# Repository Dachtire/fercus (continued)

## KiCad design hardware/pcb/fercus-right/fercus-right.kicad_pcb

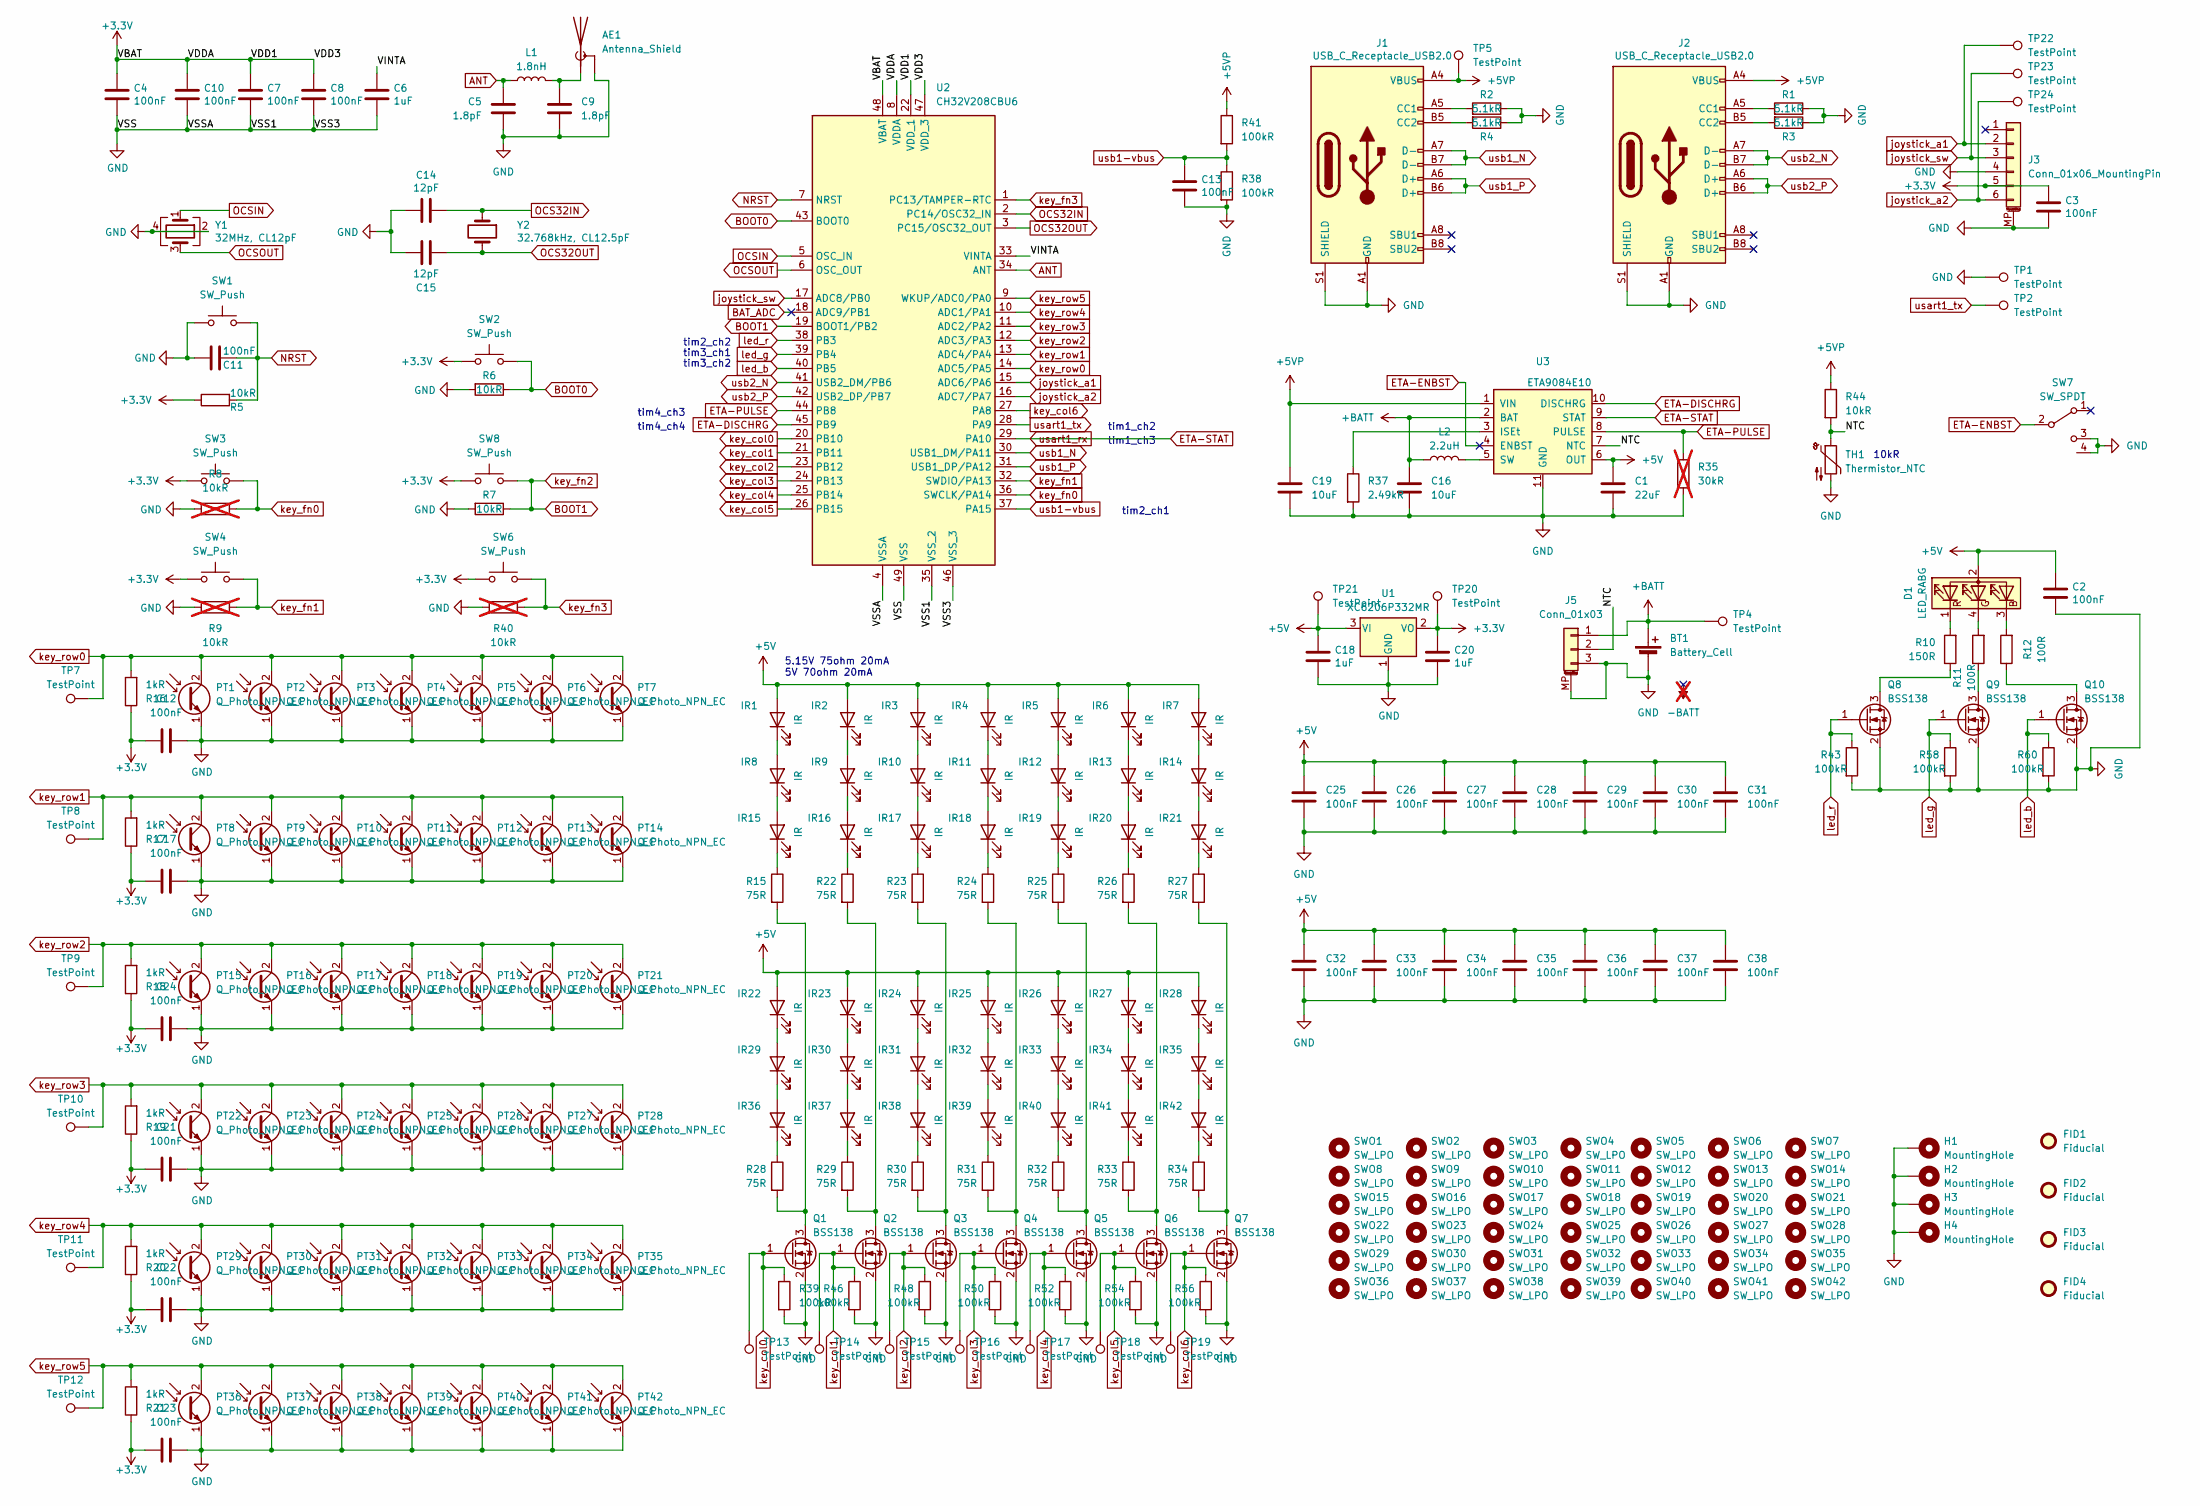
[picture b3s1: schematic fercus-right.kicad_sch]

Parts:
AE1: Antenna_Shield; ANT-F-1-2.4G-1.2MM-FR4-WCH_Right_NoMask
BT1: Battery_Cell
C1: 22uF; C_0603_1608Metric
C2, C3, C12, C13, C17, C21, C22, C23, C24, C25, C26, C27, C28, C29, C30, C31, C32, C33, C34, C35, C36, C37, C38: 100nF; C_0603_1608Metric
C4, C7, C8, C10, C11: 100nF; C_0402_1005Metric
C5, C9: 1.8pF; C_0402_1005Metric
C6: 1uF; C_0402_1005Metric
C14, C15: 12pF; C_0402_1005Metric
C16: 10uF; C_0603_1608Metric
C18, C20: 1uF; C_0603_1608Metric
C19: 10uF; C_0805_2012Metric
D1: LED_RABG; Everlight_LED_RGB_PLCC-4
FID1, FID2, FID3, FID4: Fiducial; Fiducial_1mm_Mask3mm
H1, H2, H3, H4: MountingHole; MountingHole_2.2mm_M2_ISO14580_Pad
IR1, IR2, IR3, IR4, IR5, IR6, IR7, IR8, IR9, IR10, IR11, IR12, IR13, IR14, IR15, IR16, IR17, IR18, IR19, IR20, IR21, IR22, IR23, IR24, IR25, IR26, IR27, IR28, IR29, IR30, IR31, IR32, IR33, IR34, IR35, IR36, IR37, IR38, IR39, IR40, IR41, IR42: IR; KTR-0602IRC
J1, J2: USB_C_Receptacle_USB2.0; USB_C_Receptacle_HRO_TYPE-C-31-M-12
J3: Conn_01x06_MountingPin; Jushuo_AFC42-S06FMA-1H_1x6-1MP_P0.50_Horizontal
J5: Conn_01x03; Molex_PicoBlade_53261-0371_1x03-1MP_P1.25mm_Horizontal
L1: 1.8nH; L_0402_1005Metric
L2: 2.2uH; L_Sunlord_MWSA0402S
PT1, PT2, PT3, PT4, PT5, PT6, PT7, PT8, PT9, PT10, PT11, PT12, PT13, PT14, PT15, PT16, PT17, PT18, PT19, PT20, PT21, PT22, PT23, PT24, PT25, PT26, PT27, PT28, PT29, PT30, PT31, PT32, PT33, PT34, PT35, PT36, PT37, PT38, PT39, PT40, PT41, PT42: Q_Photo_NPN_EC; KTR-0602PTD
Q1, Q2, Q3, Q4, Q5, Q6, Q7, Q8, Q9, Q10: BSS138; SOT-23
R1, R2, R3, R4: 5.1kR; R_0603_1608Metric
R5, R6, R7, R44: 10kR; R_0603_1608Metric
R8, R9, R40: 10kR; R_0603_1608Metric; not fitted
R10: 150R; R_0603_1608Metric
R11, R12: 100R; R_0603_1608Metric
R15, R22, R23, R24, R25, R26, R27, R28, R29, R30, R31, R32, R33, R34: 75R; R_0603_1608Metric
R16, R17, R18, R19, R20, R21: 1kR; R_0603_1608Metric
R35: 30kR; R_0603_1608Metric; not fitted
R37: 2.49kR; R_0603_1608Metric
R38, R39, R41, R43, R46, R48, R50, R52, R54, R56, R58, R60: 100kR; R_0603_1608Metric
SW1, SW2, SW3, SW4, SW6, SW8: SW_Push; SW_SPST_TL3342
SW7: SW_SPDT; SW_SPDT_PCM12
SWO1, SWO2, SWO3, SWO4, SWO5, SWO6, SWO7, SWO8, SWO9, SWO10, SWO11, SWO12, SWO13, SWO14, SWO15, SWO16, SWO17, SWO18, SWO19, SWO20, SWO21, SWO22, SWO23, SWO24, SWO25, SWO26, SWO27, SWO28, SWO29, SWO30, SWO31, SWO32, SWO33, SWO34, SWO35, SWO36, SWO37, SWO38, SWO39, SWO40, SWO41, SWO42: SW_LPO; SW_RAESHA_Low_Profile_Optical
TH1: Thermistor_NTC; R_0603_1608Metric
TP1, TP2, TP4, TP5, TP7, TP8, TP9, TP10, TP11, TP12, TP13, TP14, TP15, TP16, TP17, TP18, TP19, TP20, TP21, TP22, TP23, TP24: TestPoint; TestPoint_Pad_D1.0mm
U1: XC6206P332MR; SOT-23-3
U2: CH32V208CBU6; QFN-48-1EP_5x5mm_P0.35mm_EP3.7x3.7mm_ThermalVias_Drill0.3mm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
U3: ETA9084E10; SSOP-10-1EP_3.9x4.9mm_P1.00mm_EP2.4x2.8mm_ThermalVias_Drill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
Y1: 32MHz, CL12pF; Crystal_SMD_2016-4Pin_2.0x1.6mm
Y2: 32.768kHz, CL12.5pF; Crystal_SMD_2012-2Pin_2.0x1.2mm

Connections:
+3.3V: C3.1, C4.1, C7.1, C8.1, C10.1, C12.1, C17.1, C20.1, C21.1, C22.1, C23.1, C24.1, J3.5, R5.1, R16.1, R17.1, R18.1, R19.1, R20.1, R21.1, SW2.1, SW3.1, SW4.1, SW6.1, SW8.1, TP20.1, U1.2 (VO), U2.8 (VDDA), U2.22 (VDD_1), U2.47 (VDD_3), U2.48 (VBAT)
+5V: C1.1, C2.1, C18.1, C25.2, C26.2, C27.2, C28.2, C29.2, C30.2, C31.2, C32.2, C33.2, C34.2, C35.2, C36.2, C37.2, C38.2, D1.2 (A), IR1.2 (A), IR2.2 (A), IR3.2 (A), IR4.2 (A), IR5.2 (A), IR6.2 (A), IR7.2 (A), IR22.2 (A), IR23.2 (A), IR24.2 (A), IR25.2 (A), IR26.2 (A), IR27.2 (A), IR28.2 (A), TP21.1, U1.3 (VI), U3.6 (OUT)
+5VP: C19.1, J1.A4 (VBUS), J1.A9 (VBUS), J1.B4 (VBUS), J1.B9 (VBUS), J2.A4 (VBUS), J2.A9 (VBUS), J2.B4 (VBUS), J2.B9 (VBUS), R41.1, R44.1, TP5.1, U3.1 (VIN)
+BATT: BT1.1 (+), C16.1, J5.1, L2.1, TP4.1, U3.2 (BAT)
/NTC: J5.2, R44.2, TH1.1, U3.7 (NTC)
/VINTA: C6.1, U2.33 (VINTA)
ANT: C5.1, L1.1, U2.34 (ANT)
BAT_ADC: U2.18 (ADC9/PB1)
BOOT0: R6.1, SW2.2, U2.43 (BOOT0)
BOOT1: R7.1, SW8.2, U2.19 (BOOT1/PB2)
ETA-DISCHRG: U2.45 (PB9), U3.10 (DISCHRG)
ETA-ENBST: SW7.2 (B), U3.4 (ENBST)
ETA-PULSE: R35.1, U2.44 (PB8), U3.8 (PULSE)
ETA-STAT: U2.29 (PA10), U3.9 (STAT)
GND: AE1.2 (Shield), BT1.2 (-), C1.2, C2.2, C3.2, C4.2, C5.2, C6.2, C7.2, C8.2, C9.2, C10.2, C11.2, C12.2, C13.2, C14.2, C15.2, C16.2, C17.2, C18.2, C19.2, C20.2, C21.2, C22.2, C23.2, C24.2, C25.1, C26.1, C27.1, C28.1, C29.1, C30.1, C31.1, C32.1, C33.1, C34.1, C35.1, C36.1, C37.1, C38.1, H1.1, H2.1, H3.1, H4.1, J1.A1 (GND), J1.A12 (GND), J1.B1 (GND), J1.B12 (GND), J1.S1 (SHIELD), J2.A1 (GND), J2.A12 (GND), J2.B1 (GND), J2.B12 (GND), J2.S1 (SHIELD), J3.4, J3.MP (MountPin), J5.3, J5.MP (MountPin), PT1.1 (E), PT2.1 (E), PT3.1 (E), PT4.1 (E), PT5.1 (E), PT6.1 (E), PT7.1 (E), PT8.1 (E), PT9.1 (E), PT10.1 (E), PT11.1 (E), PT12.1 (E), PT13.1 (E), PT14.1 (E), PT15.1 (E), PT16.1 (E), PT17.1 (E), PT18.1 (E), PT19.1 (E), PT20.1 (E), PT21.1 (E), PT22.1 (E), PT23.1 (E), PT24.1 (E), PT25.1 (E), PT26.1 (E), PT27.1 (E), PT28.1 (E), PT29.1 (E), PT30.1 (E), PT31.1 (E), PT32.1 (E), PT33.1 (E), PT34.1 (E), PT35.1 (E), PT36.1 (E), PT37.1 (E), PT38.1 (E), PT39.1 (E), PT40.1 (E), PT41.1 (E), PT42.1 (E), Q1.2 (S), Q2.2 (S), Q3.2 (S), Q4.2 (S), Q5.2 (S), Q6.2 (S), Q7.2 (S), Q8.2 (S), Q9.2 (S), Q10.2 (S), R1.1, R2.1, R3.1, R4.1, R6.2, R7.2, R8.2, R9.2, R35.2, R37.2, R38.2, R39.2, R40.2, R43.2, R46.2, R48.2, R50.2, R52.2, R54.2, R56.2, R58.2, R60.2, SW1.1, SW7.3 (C), SW7.4, TH1.2, TP1.1, U1.1 (GND), U2.4 (VSSA), U2.35 (VSS_2), U2.46 (VSS_3), U2.49 (VSS), U3.11 (GND), Y1.2, Y1.4
NRST: C11.1, R5.2, SW1.2, U2.7 (NRST)
unnamed: AE1.1 (A), C9.1, L1.2
unnamed: D1.3 (BK), R12.2
unnamed: D1.4 (GK), R11.2
unnamed: D1.1 (RK), R10.2
unnamed: IR1.1 (K), IR8.2 (A)
unnamed: IR2.1 (K), IR9.2 (A)
unnamed: IR3.1 (K), IR10.2 (A)
unnamed: IR10.1 (K), IR17.2 (A)
unnamed: IR4.1 (K), IR11.2 (A)
unnamed: IR11.1 (K), IR18.2 (A)
unnamed: IR5.1 (K), IR12.2 (A)
unnamed: IR12.1 (K), IR19.2 (A)
unnamed: IR6.1 (K), IR13.2 (A)
unnamed: IR13.1 (K), IR20.2 (A)
unnamed: IR7.1 (K), IR14.2 (A)
unnamed: IR14.1 (K), IR21.2 (A)
unnamed: IR8.1 (K), IR15.2 (A)
unnamed: IR15.1 (K), R15.1
unnamed: IR9.1 (K), IR16.2 (A)
unnamed: IR16.1 (K), R22.1
unnamed: IR17.1 (K), R23.1
unnamed: IR18.1 (K), R24.1
unnamed: IR19.1 (K), R25.1
unnamed: IR20.1 (K), R26.1
unnamed: IR21.1 (K), R27.1
unnamed: IR22.1 (K), IR29.2 (A)
unnamed: IR23.1 (K), IR30.2 (A)
unnamed: IR24.1 (K), IR31.2 (A)
unnamed: IR25.1 (K), IR32.2 (A)
unnamed: IR26.1 (K), IR33.2 (A)
unnamed: IR27.1 (K), IR34.2 (A)
unnamed: IR28.1 (K), IR35.2 (A)
unnamed: IR29.1 (K), IR36.2 (A)
unnamed: IR30.1 (K), IR37.2 (A)
unnamed: IR31.1 (K), IR38.2 (A)
unnamed: IR32.1 (K), IR39.2 (A)
unnamed: IR33.1 (K), IR40.2 (A)
unnamed: IR34.1 (K), IR41.2 (A)
unnamed: IR35.1 (K), IR42.2 (A)
unnamed: IR36.1 (K), R28.1
unnamed: IR37.1 (K), R29.1
unnamed: IR38.1 (K), R30.1
unnamed: IR39.1 (K), R31.1
unnamed: IR40.1 (K), R32.1
unnamed: IR41.1 (K), R33.1
unnamed: IR42.1 (K), R34.1
unnamed: J1.A5 (CC1), R2.2
unnamed: J1.B5 (CC2), R4.2
unnamed: J2.A5 (CC1), R1.2
unnamed: J2.B5 (CC2), R3.2
unnamed: Q1.3 (D), R15.2, R28.2
unnamed: Q2.3 (D), R22.2, R29.2
unnamed: Q3.3 (D), R23.2, R30.2
unnamed: Q4.3 (D), R24.2, R31.2
unnamed: Q5.3 (D), R25.2, R32.2
unnamed: Q6.3 (D), R26.2, R33.2
unnamed: Q7.3 (D), R27.2, R34.2
unnamed: Q8.3 (D), R10.1
unnamed: Q9.3 (D), R11.1
unnamed: Q10.3 (D), R12.1
unnamed: R37.1, U3.3 (ISEt)
unnamed: L2.2, U3.5 (SW)
OCS32IN: C14.1, U2.2 (PC14/OSC32_IN), Y2.1
OCS32OUT: C15.1, U2.3 (PC15/OSC32_OUT), Y2.2
OCSIN: U2.5 (OSC_IN), Y1.1
OCSOUT: U2.6 (OSC_OUT), Y1.3
joystick_a1: J3.2, TP22.1, U2.15 (ADC6/PA6)
joystick_a2: J3.6, TP24.1, U2.16 (ADC7/PA7)
joystick_sw: J3.3, TP23.1, U2.17 (ADC8/PB0)
key_col0: Q1.1 (G), R39.1, TP13.1, U2.20 (PB10)
key_col1: Q2.1 (G), R46.1, TP14.1, U2.21 (PB11)
key_col2: Q3.1 (G), R48.1, TP15.1, U2.23 (PB12)
key_col3: Q4.1 (G), R50.1, TP16.1, U2.24 (PB13)
key_col4: Q5.1 (G), R52.1, TP17.1, U2.25 (PB14)
key_col5: Q6.1 (G), R54.1, TP18.1, U2.26 (PB15)
key_col6: Q7.1 (G), R56.1, TP19.1, U2.27 (PA8)
key_fn0: R8.1, SW3.2, U2.36 (SWCLK/PA14)
key_fn1: R9.1, SW4.2, U2.32 (SWDIO/PA13)
key_fn3: R40.1, SW6.2, U2.1 (PC13/TAMPER-RTC)
key_row0: PT1.2 (C), PT2.2 (C), PT3.2 (C), PT4.2 (C), PT5.2 (C), PT6.2 (C), PT7.2 (C), R16.2, TP7.1, U2.14 (ADC5/PA5)
key_row1: PT8.2 (C), PT9.2 (C), PT10.2 (C), PT11.2 (C), PT12.2 (C), PT13.2 (C), PT14.2 (C), R17.2, TP8.1, U2.13 (ADC4/PA4)
key_row2: PT15.2 (C), PT16.2 (C), PT17.2 (C), PT18.2 (C), PT19.2 (C), PT20.2 (C), PT21.2 (C), R18.2, TP9.1, U2.12 (ADC3/PA3)
key_row3: PT22.2 (C), PT23.2 (C), PT24.2 (C), PT25.2 (C), PT26.2 (C), PT27.2 (C), PT28.2 (C), R19.2, TP10.1, U2.11 (ADC2/PA2)
key_row4: PT29.2 (C), PT30.2 (C), PT31.2 (C), PT32.2 (C), PT33.2 (C), PT34.2 (C), PT35.2 (C), R20.2, TP11.1, U2.10 (ADC1/PA1)
key_row5: PT36.2 (C), PT37.2 (C), PT38.2 (C), PT39.2 (C), PT40.2 (C), PT41.2 (C), PT42.2 (C), R21.2, TP12.1, U2.9 (WKUP/ADC0/PA0)
led_b: Q10.1 (G), R60.1, U2.40 (PB5)
led_g: Q9.1 (G), R58.1, U2.39 (PB4)
led_r: Q8.1 (G), R43.1, U2.38 (PB3)
usart1_tx: TP2.1, U2.28 (PA9)
usb1-vbus: C13.1, R38.1, R41.2, U2.37 (PA15)
usb1_N: J1.A7 (D-), J1.B7 (D-), U2.30 (USB1_DM/PA11)
usb1_P: J1.A6 (D+), J1.B6 (D+), U2.31 (USB1_DP/PA12)
usb2_N: J2.A7 (D-), J2.B7 (D-), U2.41 (USB2_DM/PB6)
usb2_P: J2.A6 (D+), J2.B6 (D+), U2.42 (USB2_DP/PB7)

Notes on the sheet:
10kR
tim4_ch4
tim1_ch3
tim2_ch2
5.15V 75ohm 20mA 5V 70ohm 20mA
tim2_ch1
tim4_ch3
tim1_ch2
tim3_ch2
tim3_ch1

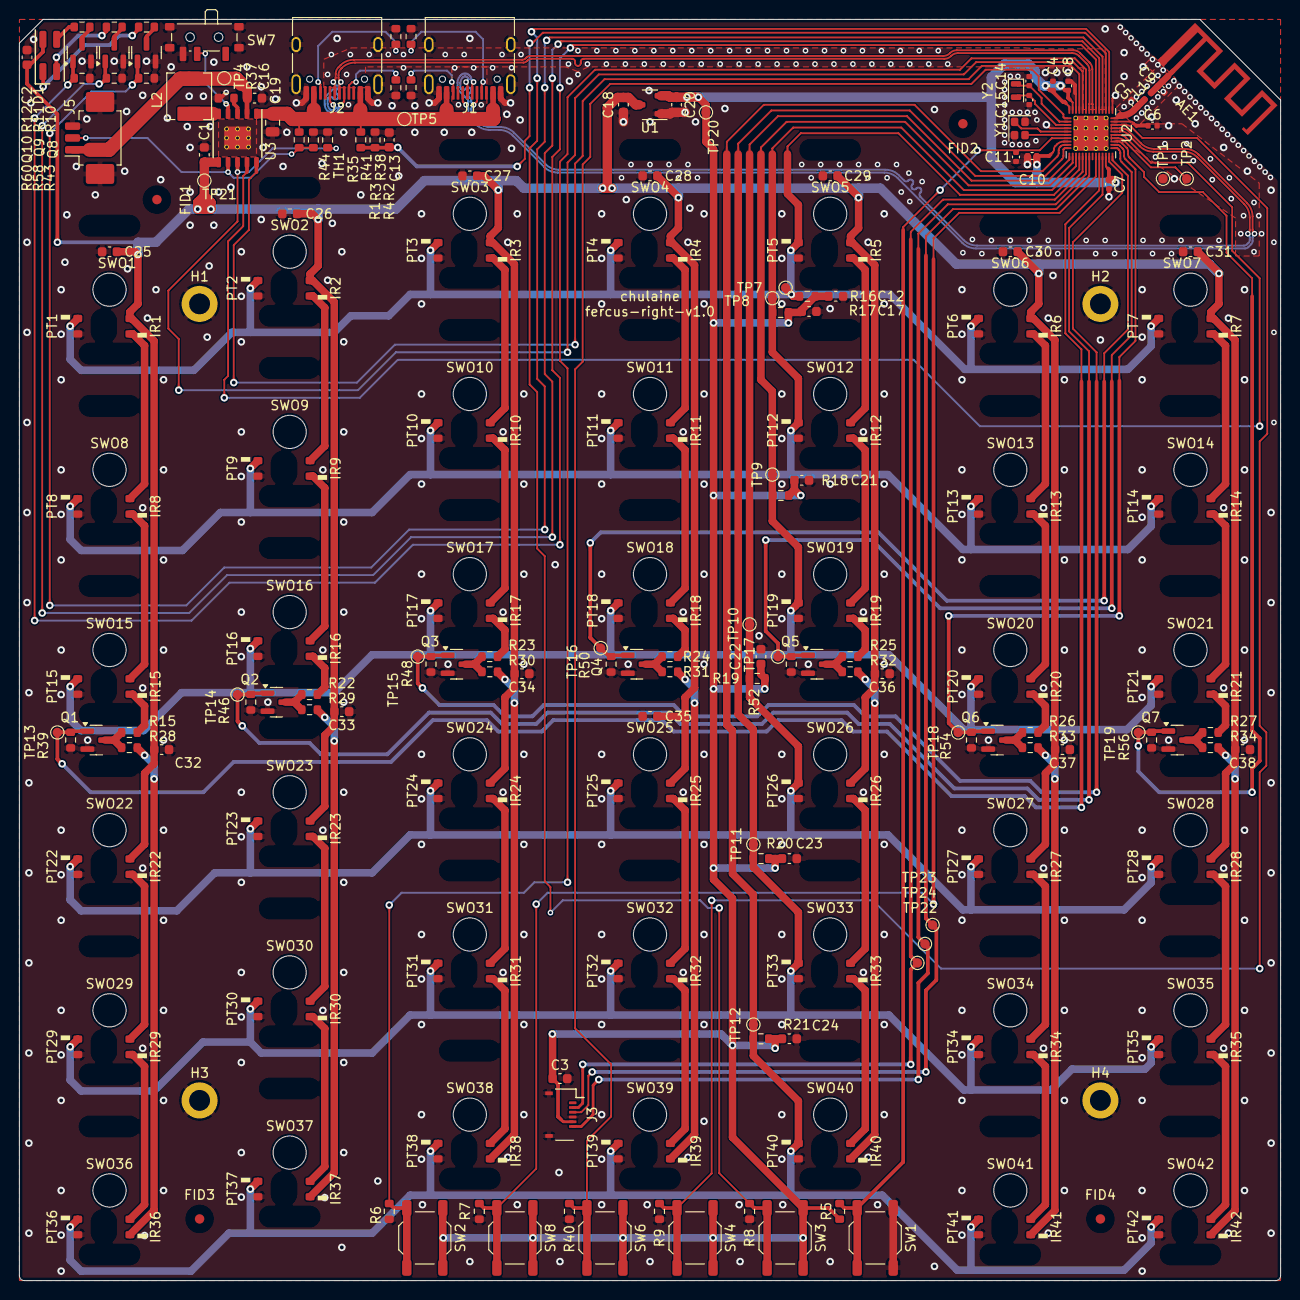
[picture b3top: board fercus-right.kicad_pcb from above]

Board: 2 copper layers, 133.0 x 133.0 mm, 273 parts (0 on the bottom side), 109 nets.

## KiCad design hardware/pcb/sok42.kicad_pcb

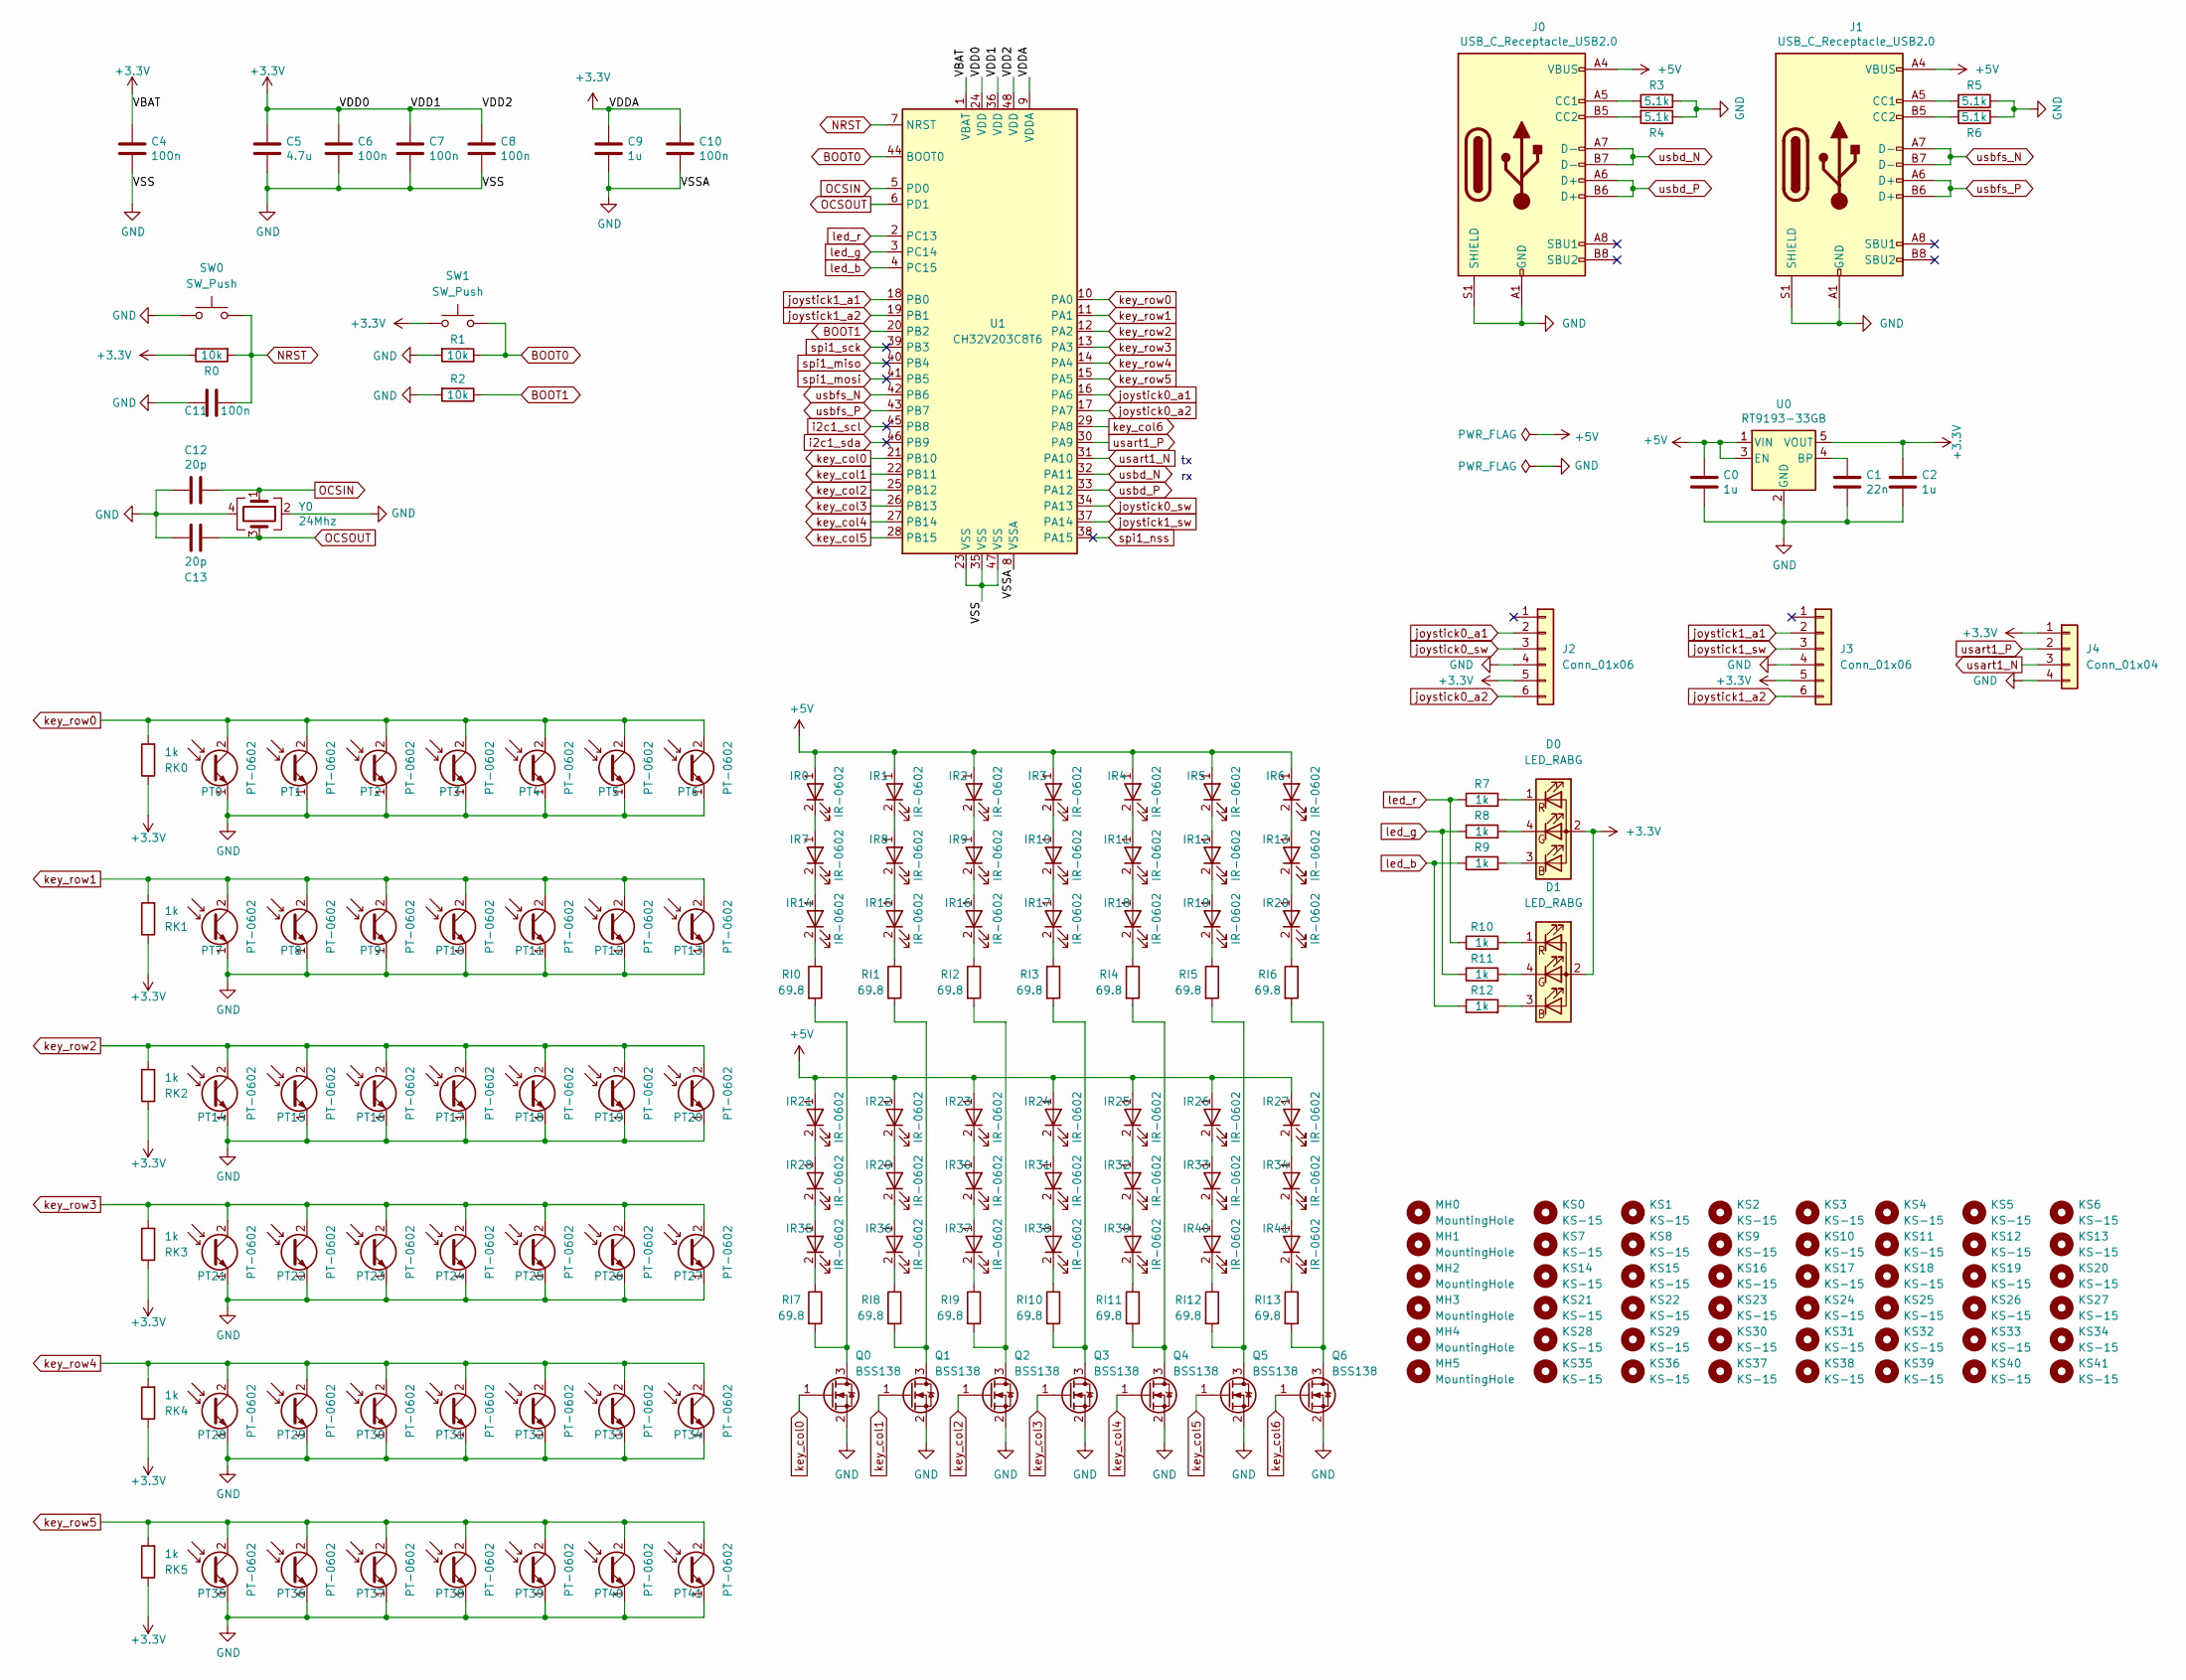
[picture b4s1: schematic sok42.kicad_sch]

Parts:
C0, C2, C9: 1u; RC_0603_1608Metric
C1: 22n; RC_0603_1608Metric
C4, C6, C7, C8, C10, C11: 100n; RC_0603_1608Metric
C5: 4.7u; RC_1206_3216Metric
C12, C13: 20p; RC_0603_1608Metric
D0, D1: LED_RABG; LED_RGB_PLCC4
IR0, IR1, IR2, IR3, IR4, IR5, IR6, IR7, IR8, IR9, IR10, IR11, IR12, IR13, IR14, IR15, IR16, IR17, IR18, IR19, IR20, IR21, IR22, IR23, IR24, IR25, IR26, IR27, IR28, IR29, IR30, IR31, IR32, IR33, IR34, IR35, IR36, IR37, IR38, IR39, IR40, IR41: IR-0602
J0, J1: USB_C_Receptacle_USB2.0; USB_C_Receptacle_HRO_TYPE-C-31-M-12
J2, J3: Conn_01x06; Jushuo_AFC42-S06FMA-1H_1x6-1MP_P0.50_Horizontal
J4: Conn_01x04; Harwin_M20-89004xx_1x04_P2.54mm_Horizontal
KS0, KS1, KS2, KS3, KS4, KS5, KS6, KS7, KS8, KS9, KS10, KS11, KS12, KS13, KS14, KS15, KS16, KS17, KS18, KS19, KS20, KS21, KS22, KS23, KS24, KS25, KS26, KS27, KS28, KS29, KS30, KS31, KS32, KS33, KS34, KS35, KS36, KS37, KS38, KS39, KS40, KS41: KS-15; KS-LP
MH0, MH1, MH2, MH3: MountingHole; MountingHole_3.2mm_M3
MH4, MH5: MountingHole; MountingHole_4mm
PT0, PT1, PT2, PT3, PT4, PT5, PT6, PT7, PT8, PT9, PT10, PT11, PT12, PT13, PT14, PT15, PT16, PT17, PT18, PT19, PT20, PT21, PT22, PT23, PT24, PT25, PT26, PT27, PT28, PT29, PT30, PT31, PT32, PT33, PT34, PT35, PT36, PT37, PT38, PT39, PT40, PT41: PT-0602
Q0, Q1, Q2, Q3, Q4, Q5, Q6: BSS138; SOT-23
R0, R1, R2: 10k; RC_0603_1608Metric
R3, R4, R5, R6: 5.1k; RC_0603_1608Metric
R7, R8, R9, R10, R11, R12: 1k; RC_0603_1608Metric
RI0, RI1, RI2, RI3, RI4, RI5, RI6, RI7, RI8, RI9, RI10, RI11, RI12, RI13: 69.8; RC_0603_1608Metric
RK0, RK1, RK2, RK3, RK4, RK5: 1k; RC_0603_1608Metric
SW0, SW1: SW_Push; SW_SPST_PTS810
U0: RT9193-33GB; SOT-23-5
U1: CH32V203C8T6; LQFP-48_7x7mm_P0.5mm
Y0: 24Mhz; Crystal_SMD_3225-4Pin_3.2x2.5mm

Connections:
+3.3V: C2.1, C4.1, C5.1, C6.1, C7.1, C8.1, C9.1, C10.1, D0.2 (A), D1.2 (A), J2.5, J3.5, J4.1, R0.1, RK0.1, RK1.1, RK2.1, RK3.1, RK4.1, RK5.1, SW1.1, U0.5 (VOUT), U1.1 (VBAT), U1.9 (VDDA), U1.24 (VDD), U1.36 (VDD), U1.48 (VDD)
+5V: C0.1, IR0.1 (A), IR1.1 (A), IR2.1 (A), IR3.1 (A), IR4.1 (A), IR5.1 (A), IR6.1 (A), IR21.1 (A), IR22.1 (A), IR23.1 (A), IR24.1 (A), IR25.1 (A), IR26.1 (A), IR27.1 (A), J0.A4 (VBUS), J0.A9 (VBUS), J0.B4 (VBUS), J0.B9 (VBUS), J1.A4 (VBUS), J1.A9 (VBUS), J1.B4 (VBUS), J1.B9 (VBUS), U0.1 (VIN), U0.3 (EN)
BOOT0: R1.1, SW1.2, U1.44 (BOOT0)
BOOT1: R2.1, U1.20 (PB2)
GND: C0.2, C1.2, C2.2, C4.2, C5.2, C6.2, C7.2, C8.2, C9.2, C10.2, C11.2, C12.2, C13.2, J0.A1 (GND), J0.A12 (GND), J0.B1 (GND), J0.B12 (GND), J0.S1 (SHIELD), J1.A1 (GND), J1.A12 (GND), J1.B1 (GND), J1.B12 (GND), J1.S1 (SHIELD), J2.4, J3.4, J4.4, PT0.1 (E), PT1.1 (E), PT2.1 (E), PT3.1 (E), PT4.1 (E), PT5.1 (E), PT6.1 (E), PT7.1 (E), PT8.1 (E), PT9.1 (E), PT10.1 (E), PT11.1 (E), PT12.1 (E), PT13.1 (E), PT14.1 (E), PT15.1 (E), PT16.1 (E), PT17.1 (E), PT18.1 (E), PT19.1 (E), PT20.1 (E), PT21.1 (E), PT22.1 (E), PT23.1 (E), PT24.1 (E), PT25.1 (E), PT26.1 (E), PT27.1 (E), PT28.1 (E), PT29.1 (E), PT30.1 (E), PT31.1 (E), PT32.1 (E), PT33.1 (E), PT34.1 (E), PT35.1 (E), PT36.1 (E), PT37.1 (E), PT38.1 (E), PT39.1 (E), PT40.1 (E), PT41.1 (E), Q0.2 (S), Q1.2 (S), Q2.2 (S), Q3.2 (S), Q4.2 (S), Q5.2 (S), Q6.2 (S), R1.2, R2.2, R3.1, R4.1, R5.1, R6.1, SW0.1, U0.2 (GND), U1.8 (VSSA), U1.23 (VSS), U1.35 (VSS), U1.47 (VSS), Y0.2, Y0.4
NRST: C11.1, R0.2, SW0.2, U1.7 (NRST)
unnamed: C1.1, U0.4 (BP)
unnamed: D0.1 (RK), R7.2
unnamed: D0.3 (BK), R9.2
unnamed: D0.4 (GK), R8.2
unnamed: D1.1 (RK), R10.2
unnamed: D1.3 (BK), R12.2
unnamed: D1.4 (GK), R11.2
unnamed: IR0.2 (K), IR7.1 (A)
unnamed: IR1.2 (K), IR8.1 (A)
unnamed: IR2.2 (K), IR9.1 (A)
unnamed: IR3.2 (K), IR10.1 (A)
unnamed: IR10.2 (K), IR17.1 (A)
unnamed: IR4.2 (K), IR11.1 (A)
unnamed: IR11.2 (K), IR18.1 (A)
unnamed: IR5.2 (K), IR12.1 (A)
unnamed: IR12.2 (K), IR19.1 (A)
unnamed: IR6.2 (K), IR13.1 (A)
unnamed: IR13.2 (K), IR20.1 (A)
unnamed: IR7.2 (K), IR14.1 (A)
unnamed: IR14.2 (K), RI0.1
unnamed: IR8.2 (K), IR15.1 (A)
unnamed: IR15.2 (K), RI1.1
unnamed: IR9.2 (K), IR16.1 (A)
unnamed: IR16.2 (K), RI2.1
unnamed: IR17.2 (K), RI3.1
unnamed: IR18.2 (K), RI4.1
unnamed: IR19.2 (K), RI5.1
unnamed: IR20.2 (K), RI6.1
unnamed: IR21.2 (K), IR28.1 (A)
unnamed: IR22.2 (K), IR29.1 (A)
unnamed: IR23.2 (K), IR30.1 (A)
unnamed: IR24.2 (K), IR31.1 (A)
unnamed: IR25.2 (K), IR32.1 (A)
unnamed: IR26.2 (K), IR33.1 (A)
unnamed: IR27.2 (K), IR34.1 (A)
unnamed: IR28.2 (K), IR35.1 (A)
unnamed: IR29.2 (K), IR36.1 (A)
unnamed: IR30.2 (K), IR37.1 (A)
unnamed: IR31.2 (K), IR38.1 (A)
unnamed: IR32.2 (K), IR39.1 (A)
unnamed: IR33.2 (K), IR40.1 (A)
unnamed: IR34.2 (K), IR41.1 (A)
unnamed: IR35.2 (K), RI7.1
unnamed: IR36.2 (K), RI8.1
unnamed: IR37.2 (K), RI9.1
unnamed: IR38.2 (K), RI10.1
unnamed: IR39.2 (K), RI11.1
unnamed: IR40.2 (K), RI12.1
unnamed: IR41.2 (K), RI13.1
unnamed: J0.A5 (CC1), R3.2
unnamed: J0.B5 (CC2), R4.2
unnamed: J1.A5 (CC1), R5.2
unnamed: J1.B5 (CC2), R6.2
unnamed: Q0.3 (D), RI0.2, RI7.2
unnamed: Q1.3 (D), RI1.2, RI8.2
unnamed: Q2.3 (D), RI2.2, RI9.2
unnamed: Q3.3 (D), RI3.2, RI10.2
unnamed: Q4.3 (D), RI4.2, RI11.2
unnamed: Q5.3 (D), RI5.2, RI12.2
unnamed: Q6.3 (D), RI6.2, RI13.2
OCSIN: C12.1, U1.5 (PD0), Y0.1
OCSOUT: C13.1, U1.6 (PD1), Y0.3
i2c1_scl: U1.45 (PB8)
i2c1_sda: U1.46 (PB9)
joystick0_a1: J2.2, U1.16 (PA6)
joystick0_a2: J2.6, U1.17 (PA7)
joystick0_sw: J2.3, U1.34 (PA13)
joystick1_a1: J3.2, U1.18 (PB0)
joystick1_a2: J3.6, U1.19 (PB1)
joystick1_sw: J3.3, U1.37 (PA14)
key_col0: Q0.1 (G), U1.21 (PB10)
key_col1: Q1.1 (G), U1.22 (PB11)
key_col2: Q2.1 (G), U1.25 (PB12)
key_col3: Q3.1 (G), U1.26 (PB13)
key_col4: Q4.1 (G), U1.27 (PB14)
key_col5: Q5.1 (G), U1.28 (PB15)
key_col6: Q6.1 (G), U1.29 (PA8)
key_row0: PT0.2 (C), PT1.2 (C), PT2.2 (C), PT3.2 (C), PT4.2 (C), PT5.2 (C), PT6.2 (C), RK0.2, U1.10 (PA0)
key_row1: PT7.2 (C), PT8.2 (C), PT9.2 (C), PT10.2 (C), PT11.2 (C), PT12.2 (C), PT13.2 (C), RK1.2, U1.11 (PA1)
key_row2: PT14.2 (C), PT15.2 (C), PT16.2 (C), PT17.2 (C), PT18.2 (C), PT19.2 (C), PT20.2 (C), RK2.2, U1.12 (PA2)
key_row3: PT21.2 (C), PT22.2 (C), PT23.2 (C), PT24.2 (C), PT25.2 (C), PT26.2 (C), PT27.2 (C), RK3.2, U1.13 (PA3)
key_row4: PT28.2 (C), PT29.2 (C), PT30.2 (C), PT31.2 (C), PT32.2 (C), PT33.2 (C), PT34.2 (C), RK4.2, U1.14 (PA4)
key_row5: PT35.2 (C), PT36.2 (C), PT37.2 (C), PT38.2 (C), PT39.2 (C), PT40.2 (C), PT41.2 (C), RK5.2, U1.15 (PA5)
led_b: R9.1, R12.1, U1.4 (PC15)
led_g: R8.1, R11.1, U1.3 (PC14)
led_r: R7.1, R10.1, U1.2 (PC13)
spi1_miso: U1.40 (PB4)
spi1_mosi: U1.41 (PB5)
spi1_nss: U1.38 (PA15)
spi1_sck: U1.39 (PB3)
usart1_N: J4.3, U1.31 (PA10)
usart1_P: J4.2, U1.30 (PA9)
usbd_N: J0.A7 (D-), J0.B7 (D-), U1.32 (PA11)
usbd_P: J0.A6 (D+), J0.B6 (D+), U1.33 (PA12)
usbfs_N: J1.A7 (D-), J1.B7 (D-), U1.42 (PB6)
usbfs_P: J1.A6 (D+), J1.B6 (D+), U1.43 (PB7)

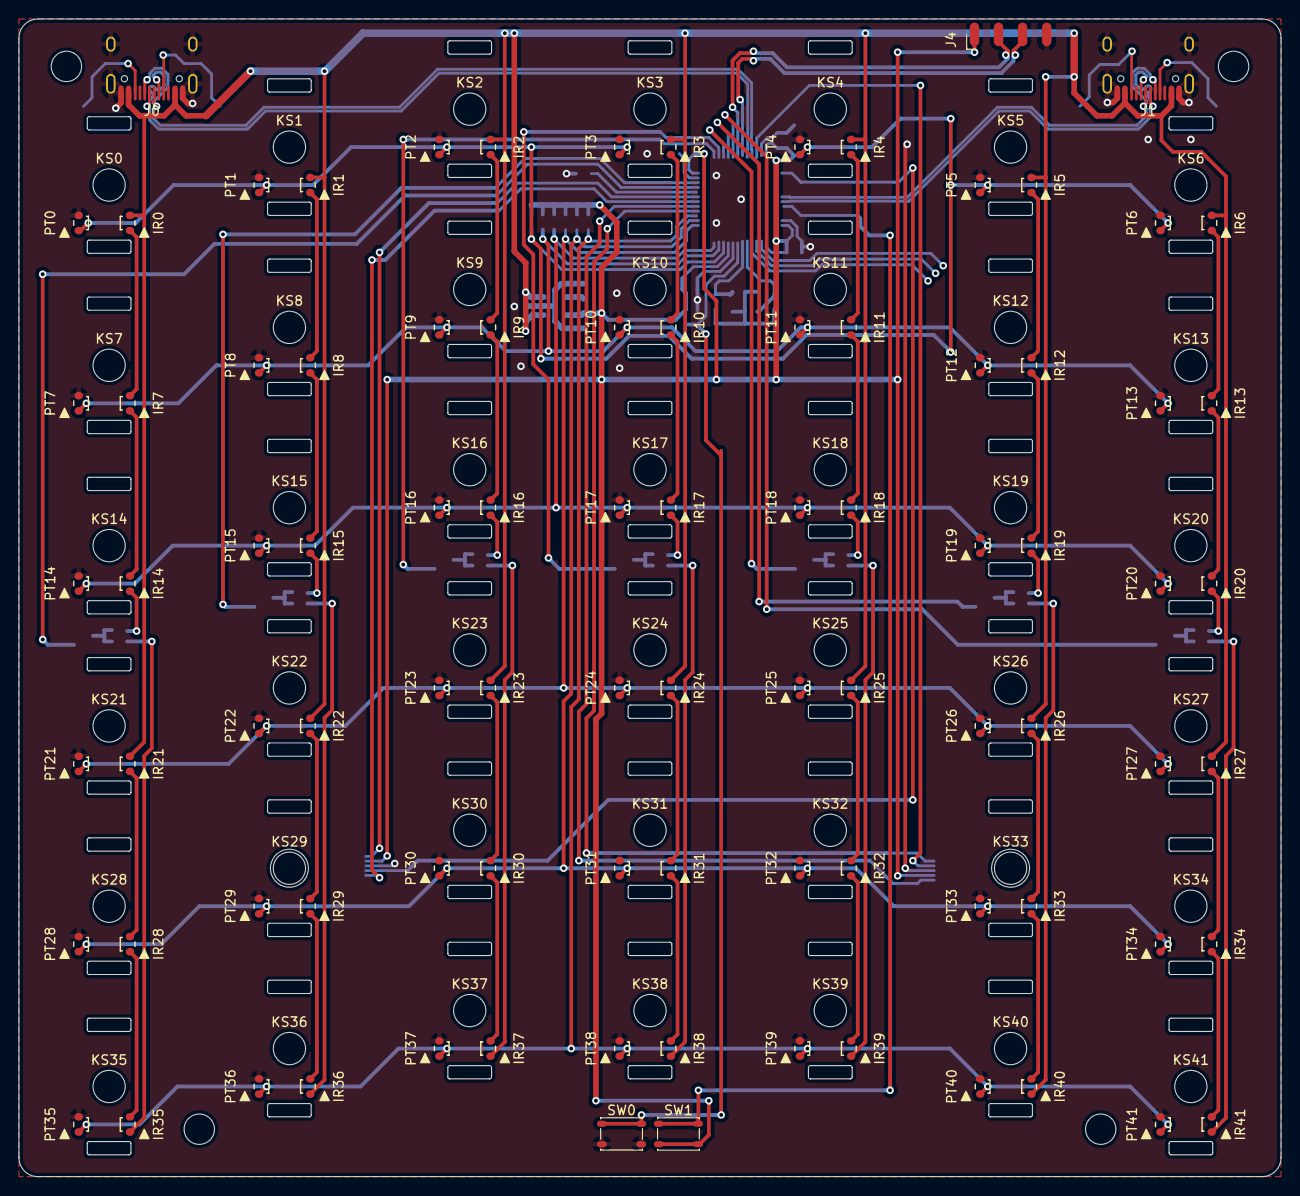
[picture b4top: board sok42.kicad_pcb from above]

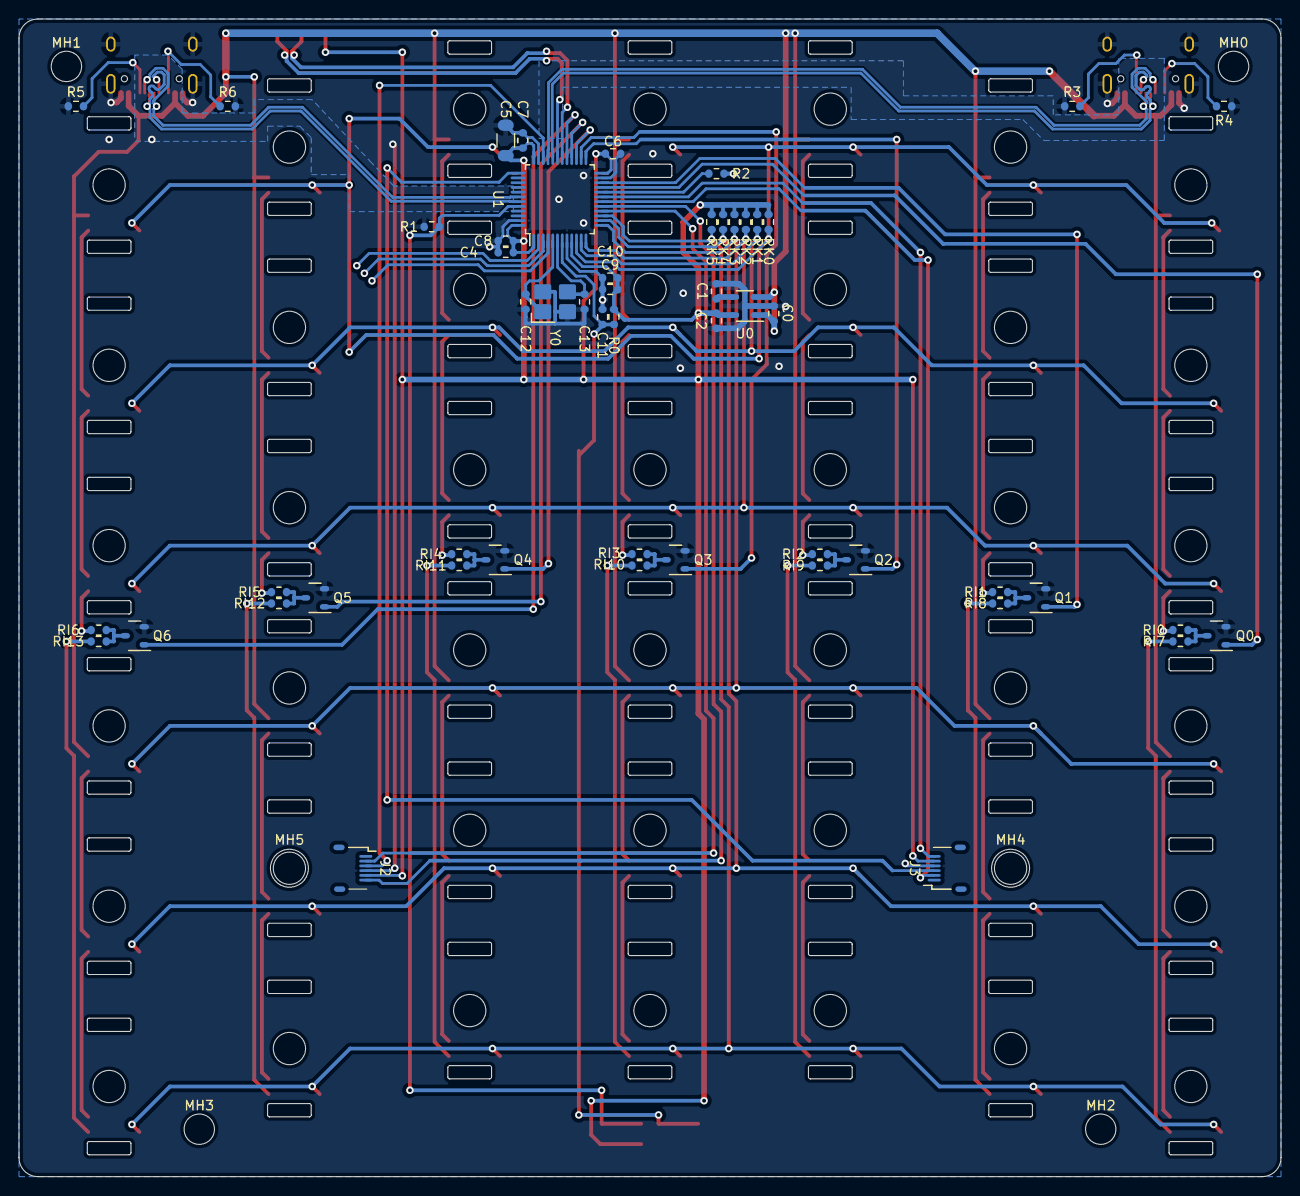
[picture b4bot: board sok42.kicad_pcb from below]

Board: 2 copper layers, 133.0 x 122.0 mm, 189 parts (58 on the bottom side), 87 nets.

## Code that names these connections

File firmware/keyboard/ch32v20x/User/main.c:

/********************************** (C) COPYRIGHT *******************************
* File Name          : main.c
* Author             : WCH
* Version            : V1.0.0
* Date               : 2021/08/08
* Description        : Main program body.
* Copyright (c) 2021 Nanjing Qinheng Microelectronics Co., Ltd.
* SPDX-License-Identifier: Apache-2.0
*******************************************************************************/ 

/*
 * @Note
 * Composite Keyboard and Mouse Example:
 * This example uses PA4-PA7 and PB12-PB15 to simulate mouse movement and keyboard
 * key pressing respectively, active low. At the same time, it also uses USART2
 * to receive data sent from the host to simulate keyboard key pressing and releasing.
 *
 */

#include "main.h"
#include "config.h"
#include "tmos-connection-mode.h"
#include "tmos-power-manager.h"
//#include "rf_sync.h"
//#include "device_config.h"

/* Global define */
__attribute__((aligned(4))) uint32_t MEM_BUF[BLE_MEMHEAP_SIZE / 4];

#if(defined(BLE_MAC)) && (BLE_MAC == TRUE)
const uint8_t MacAddr[6] = {0x84, 0xC2, 0xE4, 0x03, 0x02, 0x02};
#endif

__attribute__((section(".highcode")))
__attribute__((noinline))
void tmos_Circulation(void)
{
    while(1)
    {
//        rf_sync();
        TMOS_SystemProcess();
    }
}
/* Global Variable */

/*********************************************************************
 * @fn      main
 *
 * @brief   Main program.
 *
 * @return  none
 */
int main(void)
{
    SystemCoreClockUpdate();
    Delay_Init();

    #ifdef DEBUG
        USART_Printf_Init( 115200 );
    #endif
    PRINT("start.%s\n",__TIME__);
//    PRINT("%s\n", VER_LIB);
//    printf( "ChipID:%08x\r\n", DBGMCU_GetCHIPID() );
//    printf("SystemClk:%d\r\n",SystemCoreClock);

//    connection_mode_init(CONN_USB);
//    while (1) {}

    connection_mode = CONN_TMOS_USB;
    connection_mode_init(connection_mode);
    tmos_Circulation();
}

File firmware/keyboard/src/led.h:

#ifndef FIRMWARE_LED_H
#define FIRMWARE_LED_H

#define LED_R_PORT GPIOB
#define LED_R_PIN GPIO_Pin_3
#define LED_G_PORT GPIOB
#define LED_G_PIN GPIO_Pin_4
#define LED_B_PORT GPIOB
#define LED_B_PIN GPIO_Pin_5

#include "ch32v20x.h"

void led_gpio_init();
void led_tim_init(u16 arr, u16 psc, u16 ccp, TIM_TypeDef *tim);
void led_red_on();
void led_red_off();
void led_green_on();
void led_green_off();
void led_blue_on();
void led_blue_off();

#endif//FIRMWARE_LED_H
